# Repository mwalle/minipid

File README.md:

# minipid - an attiny based heating controller

minipid is an open source hardware and software PI controller. It's design
goal is to be cheap and easy to build. It was originally developed for the
Rancilio Siliva.

## Warning

This project uses dangerous mains voltage. Be careful!

## Features

 * cheap
 * configurable parameters, like target temperature, Kp and Ki and controlling range
 * auto off
 * built in self test
 * configuration interface on the serial line
 * display support
 * ISP support
 * fast PI controller
 * emergency off
 * error blinking, if no display is connected
 * easy to use, easy to built
 * dump parameters like temperature and output value to serial console
 * automatically detects connected display
 * open hardware and open source software

## License

The firmware is licensed under the GNU Public License version 2 and the
hardware is licensed under CERN OHL v.1.2. See `COPYING.firmware` and
`COPYING.hardware` for the complete license.

## Hardware Errata

 - [ ] SDA and SCL pull-downs are missing

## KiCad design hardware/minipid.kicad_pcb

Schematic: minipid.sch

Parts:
C1: 100n; C_Disc_D4.3mm_W1.9mm_P5.00mm
C2: 330u; CP_Radial_D8.0mm_P3.50mm
C3: 100u; CP_Radial_D6.3mm_P2.50mm
D1: DB1A70; Diode_Bridge_DIP-4_W7.62mm_P5.08mm
D2: BTA 08/600BW; TO-220-3_Horizontal_TabDown
F1: 100mA; Fuseholder_TR5_Littlefuse_No560_No460
HS1: Heatsink; Heatsink_35x26mm_1xFixation3mm_Fischer-SK486-35
J1: Mains; TerminalBlock_RND_205-00001_1x02_P5.00mm_Horizontal
J2: Load; TerminalBlock_RND_205-00001_1x02_P5.00mm_Horizontal
J3: PT1000; TerminalBlock_RND_205-00001_1x02_P5.00mm_Horizontal
J4: ISP; PinHeader_1x05_P2.54mm_Vertical
J5: Display; PinHeader_1x04_P2.54mm_Vertical
J6: UART; PinHeader_1x03_P2.54mm_Vertical
MH1, MH2, MH3, MH4: MountingHole; MountingHole_3.2mm_M3
R1, R2: 330; R_Axial_DIN0207_L6.3mm_D2.5mm_P10.16mm_Horizontal
R3: 1k; R_Axial_DIN0207_L6.3mm_D2.5mm_P10.16mm_Horizontal
TR1: 6V 0.33VA; Transformer_Breve_TEZ-22x24
U1: ATtiny45-20PU; DIP-8_W7.62mm
U2: LP2950-5.0_TO92; TO-92_Inline
U3: MOC3063M; DIP-6_W7.62mm

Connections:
AIN: J3.1, R3.2, U1.2 (XTAL1/PB3)
GND: C1.2, C2.2, C3.2, D1.2, J3.2, J4.5, J5.4, J6.3, U1.4 (GND), U2.2 (GND), U3.2
MISO_TX: J4.4, J6.1, U1.6 (PB1)
MOSI_SDA_RX: J4.3, J5.2, J6.2, U1.5 (AREF/PB0)
unnamed: C2.1, D1.1, U2.3 (VI)
unnamed: D1.3, TR1.7
unnamed: D1.4, TR1.6
unnamed: D2.1, J2.1
unnamed: D2.2, J2.2, R2.1
unnamed: D2.3, U3.4
unnamed: F1.1, J1.2
unnamed: F1.2, TR1.4
unnamed: J1.1, TR1.1
unnamed: R1.1, U3.1
unnamed: R2.2, U3.6
OUT: R1.2, U1.3 (XTAL2/PB4)
RST#: J4.1, U1.1 (~RESET~/PB5)
SCK_SCL: J4.2, J5.1, U1.7 (PB2)
VCC: C1.1, C3.1, J5.3, R3.1, U1.8 (VCC), U2.1 (VO)

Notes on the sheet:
Hot side

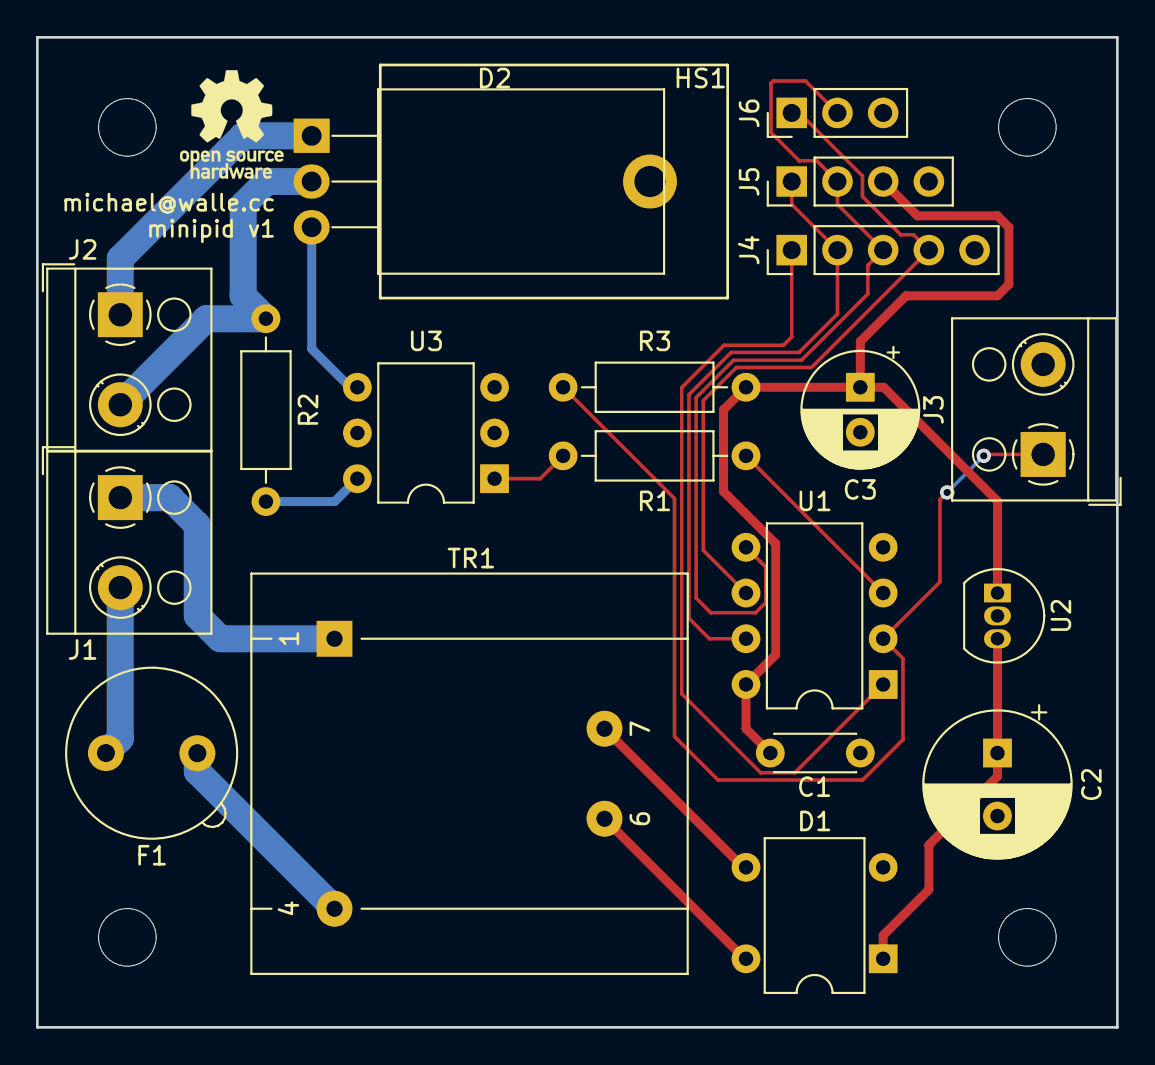
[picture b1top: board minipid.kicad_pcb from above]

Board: 2 copper layers, 60.0 x 55.0 mm, 24 parts (0 on the bottom side), 19 nets.

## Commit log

2018-10-16 adc: convert to fixed point arithmetic
2018-10-16 pid: major update
    Make derivative part a compile time option and use int16_t for the
    integrator. Remove max_error check, because internally, we calculate
    with 32 bit now. Remove float data types.
2018-10-16 pid: add simulation
2018-10-16 config: move config stuff to own file
    Also implement parser and dumper.
2018-10-16 usi: add uart_puts() and uart_puts_P()
    Also, send additional carriage return on newline.
2018-10-16 main: get rid of printf()
2018-10-16 main: print version
2018-10-18 adc: move adc stuff into own module
2018-10-18 tests: move config tests to tests/
    We use the glib testing framework to make unit tests.
2018-10-18 move from tiny44 to tiny85
    The minipid uses a tiny45/tiny85.
2018-10-18 main: print statusline periodically
2018-10-18 adc: fix init
2018-10-18 config: add init function
2018-10-18 main: enable pid controller
2018-10-19 usi: new rx handling
    There is now a RX buffer, which saturates at the end. uart_getc() will
    still return the last received character. But now it is also possible to
    poll for a received character using uart_poll().
2018-10-19 config: read values from eeprom
    Read the configration from eeprom on startup. Also add config_save() to
    save the configuration to the eeprom.
2018-10-19 main: add configuration mode
    Add a small CLI to let the user configure the controller.
2018-10-19 main: fix undefined function
2018-10-19 main: use sample_time_ms configuration parameter
    Introduce the millis() function which counts milliseconds. Also fix the
    access to uptime by using a dedicated function.
2018-10-19 tests: fix config tests
2018-10-19 adc: move pt1000 conversions to own module
    This will ease the testing.
2018-10-19 use new naming convention for volatile variables
    Prefix them with __var.
2018-10-19 new feature: emergency shutdown (wip)
2018-10-19 tests: add pt1000 tests
2018-10-21 usi: fix rx buffer
    The first bit was never written, therefore the buffer was always empty.
2018-10-21 main: fix cli
2018-10-21 main: fix uptime and sample time
2018-10-21 pid: call pid_init()
    This was missing, thus the controller wasn't working.
2018-10-30 pt1000: add degc2adc()
2018-10-30 pid: use scaled value for i_sum
    In this case, finer increments are possible. Also take the sample time
    into account.
2018-10-30 config: use PID_SCALING_SHIFT macro
2018-10-31 pid: add statusline and debug flag
2018-10-31 hardware: fix Triac name
2018-10-31 add copyright and license
2018-10-31 hardware: add schematics and gerber files
2018-10-31 add README.md
2018-12-09 main: add auto power-off support
2018-12-09 main: new compile-time option to enable CLI
2018-12-09 main: goto error state on sensor failure
    If the sensor is either not connected or it is shorted go into error
    state.
2018-12-09 main: implement emergency off
2018-12-09 main: enter configuration mode in error state
    In case the user might have something misconfigured, there is no way to
    enter configuration mode once the controller is in error state. Fix
    this.
2018-12-09 main: trap backspace input
2019-12-29 main: add reset command
2019-12-29 usi: init uart idx in every case
2019-12-29 main: show error code on i2c display
2019-12-29 pid: cast to int32 to prevent overflow
2020-03-01 enable brown-out detector
    Enable the BOD to save us from EEPROM corruption.
